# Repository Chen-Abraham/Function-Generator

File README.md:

# Function Generator

A microcontroller-based function generator built for BEE 425 at UW Bothell (Fall 2026). A Raspberry Pi Pico 2 controls an AD9833 DDS chip, and a two-stage op-amp output amplifier delivers sine, triangle, and square waves from 10 Hz to 100 kHz at up to +/-5 V. Everything runs on a custom 2-layer PCB powered from a USB wall adapter.

## Features

- Sine, triangle, and square waveforms
- 10 Hz to 100 kHz frequency range (0.1 Hz resolution)
- Adjustable amplitude, 0 to +/-5 V
- Adjustable DC offset
- OLED display with rotary encoder and push-button controls
- Runs standalone from a 5 V USB wall adapter

## How It Works

The Pico 2 reads the encoder and buttons, updates the OLED, and programs the AD9833 over SPI. The AD9833 generates the waveform on its own, so the firmware only writes registers when a setting changes. An MCP42010 digital potentiometer sets the amplitude and DC offset, and two TL072 gain stages running on +/-12 V rails bring the signal up to +/-5 V at the BNC output.

| Block | Part | Function |
| --- | --- | --- |
| Controller | Raspberry Pi Pico 2 (RP2350) | User interface and SPI control |
| Waveform | AD9833 DDS module (25 MHz) | Generates sine, triangle, square |
| Amplitude / offset | MCP42010 dual digital pot | 256-step amplitude and offset control |
| Output stage | TL072 dual op-amp | Two gain stages, ~19.5x total |
| Power | DCP010512DBP | Isolated 5 V to +/-12 V for the op-amps |
| Display | SSD1306 0.96" OLED (I2C) | Shows waveform, frequency, amplitude |
| Controls | KY-040 encoder + 3 buttons | Adjust settings, waveform, on/off, reset |
| Output | BNC jack, 51 ohm series | Signal output |

## PCB

2-layer board, 135 x 72 mm, all components on the top side. Analog and digital ground pours are separated and joined at a single point next to the AD9833.

## Pico Pinout

| Signal | Pico Pin | GPIO |
| --- | --- | --- |
| OLED SDA / SCL | 6 / 7 | GP4 / GP5 |
| Encoder A / B / Switch | 14 / 15 / 16 | GP10 / GP11 / GP12 |
| Waveform button | 19 | GP14 |
| Output on/off button | 20 | GP15 |
| Digital pot CS | 21 | GP16 |
| AD9833 FSYNC | 22 | GP17 |
| SPI SCK | 24 | GP18 |
| SPI TX | 25 | GP19 |
| Reset | 30 | RUN |

## Test Points

| Test Point | Signal | Expected |
| --- | --- | --- |
| TP1 / TP2 | +5V / +3V3 | 5 V / 3.3 V |
| TP3 / TP4 | +12V / -12V | ~+/-12 V |
| TP5 / TP6 | GND / AGND | Ground |
| TP7 | DDS output | ~0.6 Vpp |
| TP8 | Amplitude pot output | Scaled DDS signal |
| TP9 | Stage 1 output | ~4.3x TP8 |
| TP10 | Offset level | 0 to 3.3 V DC |

## Building the Firmware

Requires the Raspberry Pi Pico SDK.

```
cd software
mkdir build && cd build
cmake ..
make
```

Hold BOOTSEL while plugging in the Pico, then copy `function_generator.uf2` onto it.

## Repository Structure

```
hardware/      KiCad schematic and PCB
software/      Pico firmware (C, Pico SDK)
calculations/  Design calculations
prototype/     Breadboard prototype
mechanical/    Enclosure CAD
docs/          Documentation and images
```

## Team

- **Hardware:** Cris R. Martinez Hernandez
- **Firmware:** Abraham Yin Chen

## License

MIT License. See [LICENSE](LICENSE).

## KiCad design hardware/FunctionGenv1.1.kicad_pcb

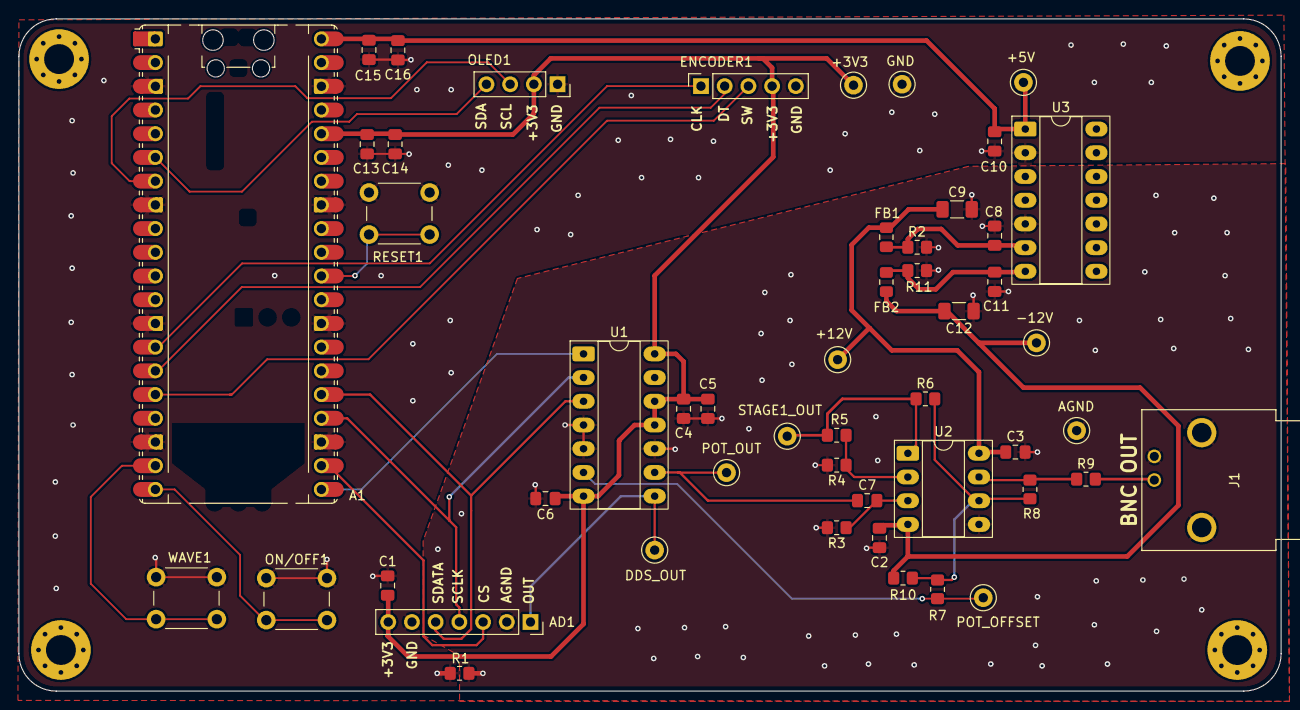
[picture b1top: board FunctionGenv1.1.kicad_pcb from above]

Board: 2 copper layers, 135.2 x 72.0 mm, 54 parts (0 on the bottom side), 29 nets.

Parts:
A1: RaspberryPi_Pico; RaspberryPi_Pico_Common_Unspecified
AD1: Conn_01x07; PinSocket_1x07_P2.54mm_Vertical
C1, C2, C3, C4, C6, C13, C15: 100n; C_0805_2012Metric_Pad1.18x1.45mm_HandSolder
C5, C7, C10, C14, C16: 10u; C_0805_2012Metric_Pad1.18x1.45mm_HandSolder
C8, C11: 1u; C_0805_2012Metric_Pad1.18x1.45mm_HandSolder
C9, C12: 10u; C_1206_3216Metric_Pad1.33x1.80mm_HandSolder
ENCODER1: KY-040 module; PinSocket_1x05_P2.54mm_Vertical
FB1, FB2: FerriteBead; L_0805_2012Metric_Pad1.15x1.40mm_HandSolder
H1, H2, H3, H4: M3_3.2mm; MountingHole_3.2mm_M3_Pad_Via
J1: 5227161-9; TE_5227161-9
OLED1: OLED_SSD1306_I2C; PinSocket_1x04_P2.54mm_Vertical
ON/OFF1: SW_Push; SW_PUSH_6mm_H5mm
R1: 0; R_0805_2012Metric_Pad1.20x1.40mm_HandSolder
R2, R11: 2.7k; R_0805_2012Metric_Pad1.20x1.40mm_HandSolder
R3: 100k; R_0805_2012Metric_Pad1.20x1.40mm_HandSolder
R4: 1k; R_0805_2012Metric_Pad1.20x1.40mm_HandSolder
R5, R6: 3.3k; R_0805_2012Metric_Pad1.20x1.40mm_HandSolder
R7: 4.7k; R_0805_2012Metric_Pad1.20x1.40mm_HandSolder
R8: 15k; R_0805_2012Metric_Pad1.20x1.40mm_HandSolder
R9: 51; R_0805_2012Metric_Pad1.20x1.40mm_HandSolder
R10: 33k; R_0805_2012Metric_Pad1.20x1.40mm_HandSolder
RESET1: SW_Push; SW_PUSH_6mm_H5mm
TP1, TP2, TP3, TP5: WHITE 5002; TestPoint_Keystone_5000-5004_Miniature
TP4, TP7, TP8, TP10: RED 5000; TestPoint_Keystone_5000-5004_Miniature
TP6, TP9: BLACK 5001; TestPoint_Keystone_5000-5004_Miniature
U1: MCP42010; DIP-14_W7.62mm_Socket_LongPads
U2: TL072; DIP-8_W7.62mm_Socket_LongPads
U3: DCP010512DBP; DIP-14_W7.62mm_Socket_LongPads
WAVE1: SW_Push; SW_PUSH_6mm_H5mm

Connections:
+3V3: A1.36 (3V3), AD1.7, C1.1, C4.1, C5.1, C6.1, C13.1, C14.1, ENCODER1.4, OLED1.2, TP8.1, U1.7 (PA1), U1.11 (~RS), U1.12 (~SHDN), U1.14 (VDD)
+5V: A1.40 (VBUS), C10.1, C15.1, C16.1, TP10.1, U3.1 (VS)
+12V: C3.1, C9.1, FB1.2, TP4.1, U2.8 (V+)
-12V: C2.1, C12.1, FB2.2, R10.1, TP7.1, U2.4 (V-)
/Analog/+VOUT: C8.1, FB1.1, R2.1, U3.6 (+VOUT)
/Analog/-VOUT: C11.1, FB2.1, R11.1, U3.7 (-VOUT)
/Analog/BNC_OUT: J1.1, R9.2
/Analog/POT_OFFSET: R7.1, TP3.1, U1.6 (PW1)
/Analog/POT_OUT: C7.1, TP2.1, U1.9 (PW0)
/Analog/STAGE1_OUT: R5.1, R6.1, TP5.1, U2.1
/Digital/BTN_1: A1.19 (GPIO14), WAVE1.1
/Digital/BTN_2: A1.20 (GPIO15), ON/OFF1.2
/Digital/ENCODER_A: A1.14 (GPIO10), ENCODER1.1
/Digital/ENCODER_B: A1.15 (GPIO11), ENCODER1.2
/Digital/ENCODER_SW: A1.16 (GPIO12), ENCODER1.3
/Digital/OLED_SCL: A1.7 (GPIO5), OLED1.3
/Digital/OLED_SDA: A1.6 (GPIO4), OLED1.4
AGND: AD1.2, C2.2, C3.2, C4.2, C5.2, C6.2, C8.2, C9.2, C11.2, C12.2, J1.2, J1.3 (MTG), J1.4 (MTG), R1.1, R2.2, R3.2, R4.2, R11.2, TP6.1, U1.4 (VSS), U1.5 (PB1), U1.10 (PB0), U2.5 (+), U3.5 (0V_2)
DDS_CS: A1.22 (GPIO17), AD1.3
DDS_OUT: AD1.1, TP1.1, U1.8 (PA0)
DDS_SCLK: A1.24 (GPIO18), AD1.4, U1.2 (SCK)
DDS_SDATA: A1.25 (GPIO19), AD1.5, U1.3 (SI)
GND: A1.3 (GND), A1.8 (GND), A1.13 (GND), A1.18 (GND), A1.23 (GND), A1.28 (GND), A1.33 (AGND), A1.38 (GND), AD1.6, C1.2, C10.2, C13.2, C14.2, C15.2, C16.2, ENCODER1.5, OLED1.1, ON/OFF1.1, R1.2, RESET1.1, TP9.1, U3.2 (0V), WAVE1.2
unnamed: A1.30 (RUN), RESET1.2
unnamed: R8.1, R9.1, U2.7
unnamed: C7.2, R3.1, U2.3 (+)
unnamed: R4.1, R5.2, U2.2 (-)
unnamed: R6.2, R7.2, R8.2, R10.2, U2.6 (-)
POT_CS: A1.21 (GPIO16), U1.1 (~CS)

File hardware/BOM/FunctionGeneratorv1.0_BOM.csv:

Total parts cost,$67.86,,,,,,,,,,,,,,
Budget,$100.00,,,,,,,,,,,,,,
Remaining,$32.14,,,,,,,,,,,,,,
,,,,,,,,,,,,,,,
Designator,Qty,Value,Package,Spec / rating,Assembly,LCSC Part #,JLC Type,Manufacturer,MPN,Description,Supplier,Supplier Part #,Unit price,Ext. price,Notes
"C1, C2, C3, C4, C6, C13, C15",7,100n,0805,"X7R, 50 V",JLC assembly,C49678,Basic,YAGEO,CC0805KRX7R9BB104,MLCC capacitor,JLCPCB,C49678,$0.01,$0.07,C2 and C3 sit on -12V / +12V
"C5, C7, C14, C16",4,10u,0805,"X5R, 25 V",JLC assembly,C15850,Basic,Samsung Electro-Mechanics,CL21A106KAYNNNE,MLCC capacitor,JLCPCB,C15850,$0.01,$0.04,C7 is the signal coupling cap
"C8, C11",2,1u,0805,"X7R, 50 V",JLC assembly,C28323,Basic,Samsung Electro-Mechanics,CL21B105KBFNNNE,MLCC capacitor,JLCPCB,C28323,$0.03,$0.06,On +/-VOUT of the DCP
"C9, C12",2,10u,1206,"X5R, 50 V",JLC assembly,C13585,Basic,Samsung Electro-Mechanics,CL31A106KBHNNNE,MLCC capacitor,JLCPCB,C13585,$0.45,$0.90,On the +/-12V rails. X5R 50 V is fine here
C10,1,10u,0805,"X5R, 25 V",JLC assembly,C15850,Basic,Samsung Electro-Mechanics,CL21A106KAYNNNE,MLCC capacitor,JLCPCB,C15850,$0.06,$0.06,"DCP input cap. No Basic 2.2u in 0805, so this uses the same 10u Basic part as row 7. Change C10 to 10u in the schematic"
"FB1, FB2",2,120R @ 100 MHz,0805,"800 mA, DCR 0.15 ohm",JLC assembly,C5671,Extended,Sunlord,GZ2012D121TF,Ferrite bead,JLCPCB,C5671,$0.02,$0.04,"Extended part (one-time fee). This is a ferrite bead, not a 120 ohm resistor"
R1,1,0 ohm,0805,"Jumper, 125 mW",JLC assembly,C17477,Basic,UNI-ROYAL,0805W8F0000T5E,Resistor,JLCPCB,C17477,$0.01,$0.01,Single AGND-GND tie
"R2, R11",2,2.7k,0805,"1%, 125 mW",JLC assembly,C17530,Basic,UNI-ROYAL,0805W8F2701T5E,Resistor,JLCPCB,C17530,$0.01,$0.02,"DCP preloads, about 53-63 mW each, so 125 mW is fine"
R3,1,100k,0805,"1%, 125 mW",JLC assembly,C149504,Basic,UNI-ROYAL,0805W8F1003T5E,Resistor,JLCPCB,C149504,$0.01,$0.01,
R4,1,1k,0805,"1%, 125 mW",JLC assembly,C17513,Basic,UNI-ROYAL,0805W8F1001T5E,Resistor,JLCPCB,C17513,$0.01,$0.01,Stage 1 gain
"R5, R6",2,3.3k,0805,"1%, 125 mW",JLC assembly,C26010,Basic,UNI-ROYAL,0805W8F3301T5E,Resistor,JLCPCB,C26010,$0.01,$0.02,"Stage 1 / stage 2 gain. Schematic shows 3k3 and 3.3k; make them match so they merge"
R7,1,4.7k,0805,"1%, 125 mW",JLC assembly,C17673,Basic,UNI-ROYAL,0805W8F4701T5E,Resistor,JLCPCB,C17673,$0.01,$0.01,Offset input
R8,1,15k,0805,"1%, 125 mW",JLC assembly,C17475,Basic,UNI-ROYAL,0805W8F1502T5E,Resistor,JLCPCB,C17475,$0.02,$0.02,Stage 2 gain
R9,1,51 ohm,0805,"1%, 125 mW",JLC assembly,C17738,Basic,UNI-ROYAL,0805W8F510JT5E,Resistor,JLCPCB,C17738,$0.01,$0.01,Output series resistor
R10,1,33k,0805,"1%, 125 mW",JLC assembly,C17633,Basic,UNI-ROYAL,0805W8F3302T5E,Resistor,JLCPCB,C17633,$0.01,$0.01,Offset bias from -12V
U1,1,MCP42010,DIP-14,Dual 10k digital pot,Hand solder,C636805,N/A,Microchip,MCP42010-I/P,Digital potentiometer,Digikey,MCP42010-I/P-ND,$3.03,$3.03,Socketed
U2,1,TL072,DIP-8,Dual JFET op-amp,Hand solder,C7236,N/A,TI,TL072CP,Op-amp,Digikey,296-1775-5-ND,$1.20,$1.20,"Out of stock at DigiKey (50 expected 28-Dec-2026). Check lab first. DIP-8 swaps: TL072BCP, TL072ACP, ST TL072CN, or TL082CP"
U3,1,DCP010512DBP,DIP-14 footprint,"5 V in, +/-12 V out, isolated",Hand solder,C527459,N/A,TI,DCP010512DBP,DC-DC converter,Digikey,DCP010512DBP-ND,$22.66,$22.66,"Unregulated, needs the preloads"
A1,1,Pico 2 H,Module,RP2350,Hand solder,C49385029,N/A,Raspberry Pi,SC1632,"Microcontroller board, headers pre-soldered",Digikey,2648-SC1632-ND,$6.00,$6.00,Plugs into the 1x20 female headers (row 35)
AD1,1,1x7 socket,2.54 mm,Female header,Hand solder,C5342086,N/A,Sullins,PPTC071LFBN-RC,Socket for AD9833 module,Digikey,S7005-ND,$0.56,$0.56,
J1,1,BNC,Right angle,50 ohm,Hand solder,5227161-9,N/A,TE,5227161-9,BNC jack,Digikey,A32261-ND,$4.95,$4.95,Output
J2,1,1x4 socket,2.54 mm,Female header,Hand solder,C3319639,N/A,Sullins,PPTC041LFBN-RC,Socket for OLED,Digikey,S7002-ND,$0.42,$0.42,
J3,1,1x5 socket,2.54 mm,Female header,Hand solder,C3320579,N/A,Sullins,PPTC051LFBN-RC,Socket for KY-040,Digikey,S6103-ND,$0.44,$0.44,
"SW1, SW2, SW3",3,6 mm tactile,THT,,Hand solder,TS665CJ,N/A,SHOU HAN,TS665CJ,Push button,Digikey,SHOU HAN TS665CJ,$0.00,$0.00,Reset / Waveform / On-Off
"TP1, TP2, TP3, TP6",4,Test point,Keystone 5000 series,White,Hand solder,C238123,N/A,Keystone,5002,Test point,Digikey,36-5002-ND,$0.27,$1.08,
"TP4, TP5, TP8, TP9",4,Test point,Keystone 5000 series,Red,Hand solder,C5199900,N/A,Keystone,5000,Test point,Digikey,36-5000-ND,$0.27,$1.08,
"TP7, TP10",2,Test point,Keystone 5000 series,Black,Hand solder,C238122,N/A,Keystone,5001,Test point,Digikey,36-5001-ND,$0.27,$0.54,
Off board,2,DIP-14 socket,DIP-14,N/A,Hand solder,C6942122,N/A,On Shore,ED14DT,"IC socket (U1, U3)",Digikey,ED3045-5-ND,$0.52,$1.04,"0.3 in (7.62 mm) row spacing, matches the DIP-14 W7.62mm footprint"
Off board,1,DIP-8 socket,DIP-8,N/A,Hand solder,C3170507,N/A,On Shore,ED08DT,IC socket (U2),Digikey,ED3044-5-ND,$0.47,$0.47,0.3 in (7.62 mm) row spacing
Off board,2,1x20 female header,2.54 mm,N/A,Hand solder,C5845594,N/A,Sullins,PPTC201LFBN-RC,Pico sockets,Digikey,S7018-ND,$1.14,$2.28,Raises the Pico so parts on its underside clear the board
Off board,1,0.96 in OLED,Module,"SSD1306, I2C",Hand solder,N/A,N/A,ELEGOO,N/A,Display module,Amazon,N/A,$3.33,$3.33,Goes in J2
Off board,1,KY-040,Module,Rotary encoder with switch,Hand solder,N/A,N/A,DEVMO,N/A,Encoder module,Amazon,N/A,$4.50,$4.50,Goes in J3
Off board,1,AD9833 module,Module,"GY-9833, 25 MHz",Hand solder,N/A,N/A,HiLetgo,N/A,DDS module,Amazon,N/A,$12.99,$12.99,Goes in AD1
